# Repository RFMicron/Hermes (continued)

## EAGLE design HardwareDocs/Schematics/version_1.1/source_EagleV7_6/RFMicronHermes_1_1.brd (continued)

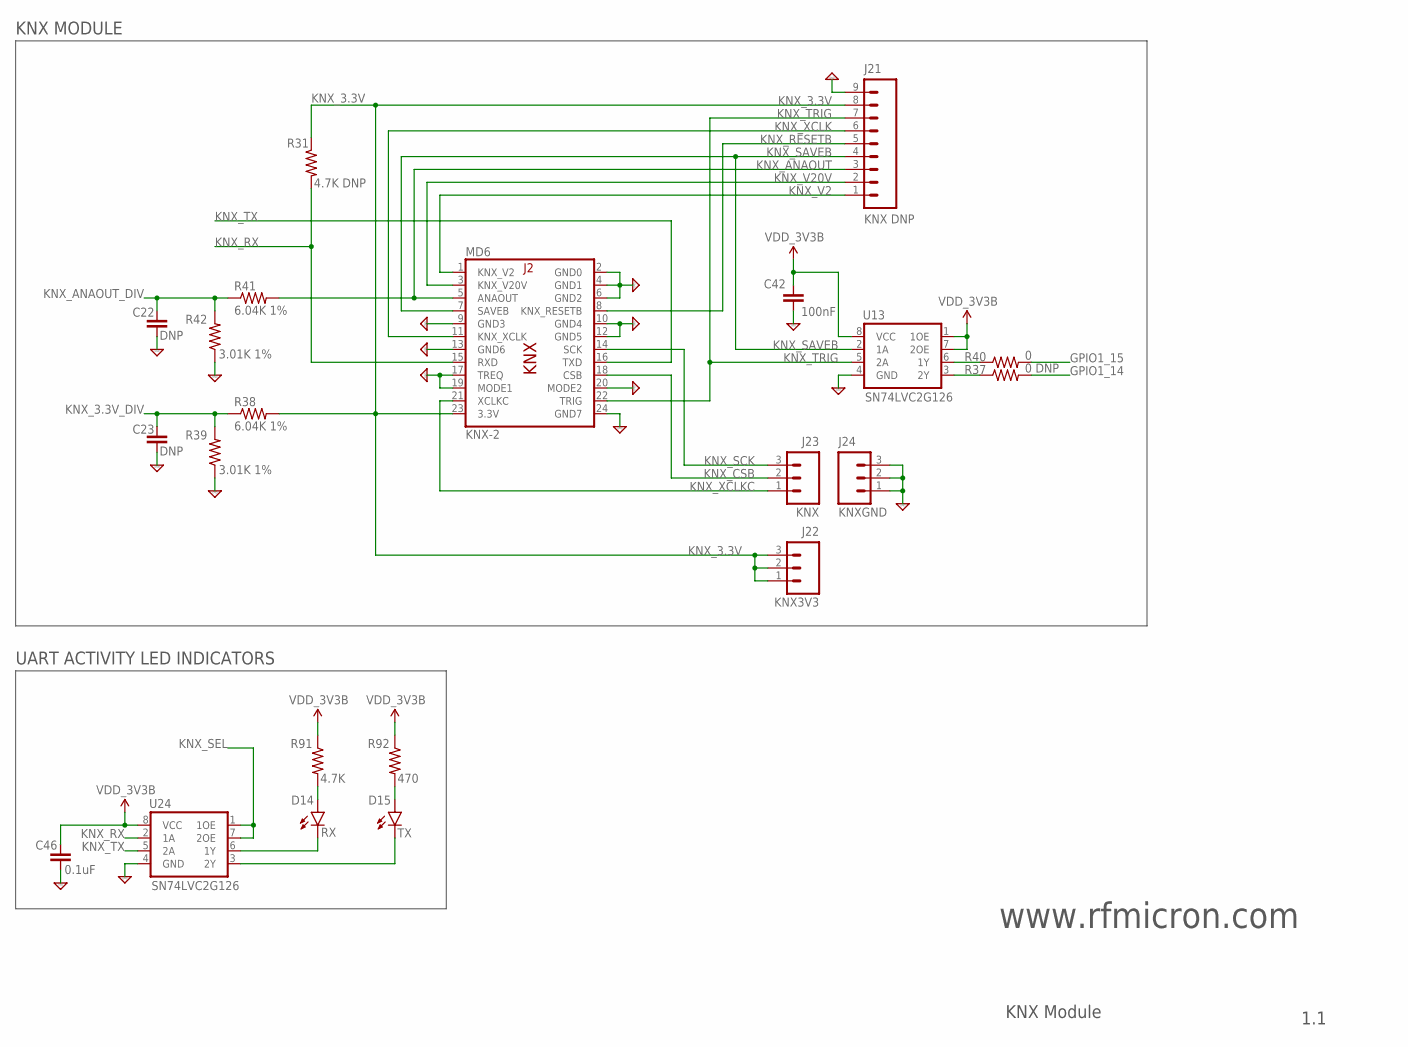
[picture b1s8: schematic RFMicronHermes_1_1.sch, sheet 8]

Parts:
C22, C23: DNP; C0603K
C42: 100nF; C0603K
C46: 0.1uF; C0603K
D14: RX; LED-1206
D15: TX; LED-1206
J21: KNX DNP; 1X09-SPECIAL
J22: KNX3V3; 1X03-SPECIAL
J23: KNX; 1X03-SPECIAL
J24: KNXGND; 1X03-SPECIAL
MD6: KNX-2; KNX-1
R31: 4.7K DNP; R0603
R37: 0 DNP; R0603
R38, R41: 6.04K 1%; R0603
R39, R42: 3.01K 1%; R0603
R40: 0; R0603
R91: 4.7K; R0603
R92: 470; R0603
U13, U24: SN74LVC2G126; SM8-TI-A

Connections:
GND: C22.2 (-), C23.2 (-), C42.2 (-), C46.1 (+), J21.9, J24.1, J24.2, J24.3, MD6.2 (GND0), MD6.4 (GND1), MD6.6 (GND2), MD6.9 (GND3), MD6.10 (GND4), MD6.12 (GND5), MD6.13 (GND6), MD6.17 (TREQ), MD6.19 (MODE1), MD6.20 (MODE2), MD6.24 (GND7), R39.1, R42.1, U13.4 (GND), U24.4 (GND); also elsewhere on the board
GPIO1_14: R37.2; also elsewhere on the board
GPIO1_15: R40.2; also elsewhere on the board
KNX_3.3V: J21.8, J22.1, J22.2, J22.3, MD6.23 (3.3V), R31.1, R38.2
KNX_3.3V_DIV: C23.1 (+), R38.1, R39.2; also elsewhere on the board
KNX_ANAOUT: J21.3, MD6.5 (ANAOUT), R41.2
KNX_ANAOUT_DIV: C22.1 (+), R41.1, R42.2; also elsewhere on the board
KNX_CSB: J23.2, MD6.18 (CSB)
KNX_RESETB: J21.5, MD6.8 (KNX_RESETB)
KNX_RX: MD6.15 (RXD), R31.2, U24.2 (1A); also elsewhere on the board
KNX_SAVEB: J21.4, MD6.7 (SAVEB), U13.2 (1A)
KNX_SCK: J23.3, MD6.14 (SCK)
KNX_SEL: U24.1 (1OE), U24.7 (2OE); also elsewhere on the board
KNX_TRIG: J21.7, MD6.22 (TRIG), U13.5 (2A)
KNX_TX: MD6.16 (TXD), U24.5 (2A); also elsewhere on the board
KNX_V2: J21.1, MD6.1 (KNX_V2)
KNX_V20V: J21.2, MD6.3 (KNX_V20V)
KNX_XCLK: J21.6, MD6.11 (KNX_XCLK)
KNX_XCLKC: J23.1, MD6.21 (XCLKC)
unnamed: R40.1, U13.6 (1Y)
unnamed: R37.1, U13.3 (2Y)
unnamed: D14.A, R91.2
unnamed: D15.A, R92.2
unnamed: D14.C, U24.6 (1Y)
unnamed: D15.C, U24.3 (2Y)
VDD_3V3B: C42.1 (+), C46.2 (-), R91.1, R92.1, U13.1 (1OE), U13.7 (2OE), U13.8 (VCC), U24.8 (VCC); also elsewhere on the board

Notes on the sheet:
www.rfmicron.com
1.1
KNX Module
UART ACTIVITY LED INDICATORS
KNX MODULE

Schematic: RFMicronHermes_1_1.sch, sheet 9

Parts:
C28: 10uF 16V; EIA3216
C29, C47: 0.1uF; C0603K
D4: DB2431200L; SC-110A-POWER_DIODE
D16: HB; LED-1206
D17: USER_LED; LED-1206
E2, E3, E4, E5, E6, E7: 1; MTHOLE4-40
F2: 3.5A; FUSE_OMNI-BLOCK-154
J11: +5V; POWER_JACK_PTH
J28: Test Connector; 2X7SM
J32: HEADER A; 2X13-SM
R76, R77, R78, R79, R80, R81: 10K; R0603
R93, R94: 4.7K; R0603
R98: 0; R0603
S1: Power; EVQ-PAC04M
S2: Reset; EVQ-PAC04M
S3: Up; EVQ-PAC04M
S4: Down; EVQ-PAC04M
S5: Right; EVQ-PAC04M
S6: Left; EVQ-PAC04M
S7: Enter; EVQ-PAC04M
U25: SN74LVC2G126; SM8-TI-A

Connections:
+5V: F2.1, J11.1 (PWR)
A0/CS: J28.1; also elsewhere on the board
A1/SI: J28.3; also elsewhere on the board
AIN4_SW: J32.7; also elsewhere on the board
AIN5_SW: J32.9; also elsewhere on the board
DOWN_BUT: R78.1, S4.1 (S), S4.2 (S1); also elsewhere on the board
EEPROM-WP: J28.13; also elsewhere on the board
ENTER_BUT: R81.1, S7.1 (S), S7.2 (S1); also elsewhere on the board
EXT_UART_RX: J28.11; also elsewhere on the board
EXT_UART_TX: J28.9; also elsewhere on the board
GND: C28.C (-), C29.2 (-), C47.1 (+), D4.A, E2.1, E3.1, E4.1, E5.1, E6.1, E7.1, J11.2 (GND), J11.3 (GNDBREAK), J28.14, J32.1, J32.13, J32.15, J32.25, R93.2, R94.2, S1.3, S1.4 (P1), S2.3, S2.4 (P1), S3.3, S3.4 (P1), S4.3, S4.4 (P1), S5.3, S5.4 (P1), S6.3, S6.4 (P1), S7.3, S7.4 (P1), U25.4 (GND); also elsewhere on the board
GPIO0_7: J32.21; also elsewhere on the board
GPIO0_20: J32.23; also elsewhere on the board
GPIO1_12: J32.14; also elsewhere on the board
GPIO1_13: J32.12; also elsewhere on the board
GPIO1_14: J32.19, R98.1; also elsewhere on the board
GPIO1_15: J32.17; also elsewhere on the board
GPIO2_3: J32.8; also elsewhere on the board
GPIO2_5: J32.10; also elsewhere on the board
I2C1_SCL: J32.16; also elsewhere on the board
I2C1_SDA: J32.18; also elsewhere on the board
LCD_TEST_V: J32.11; also elsewhere on the board
LED_HEARTBEAT: U25.2 (1A); also elsewhere on the board
LEFT_BUT: R80.1, S6.1 (S), S6.2 (S1); also elsewhere on the board
unnamed: D16.C, R93.1
unnamed: D17.C, R94.1
unnamed: R98.2, U25.5 (2A)
unnamed: D16.A, U25.6 (1Y)
unnamed: D17.A, U25.3 (2Y)
PWR_BUT: S1.1 (S), S1.2 (S1); also elsewhere on the board
RIGHT_BUT: R79.1, S5.1 (S), S5.2 (S1); also elsewhere on the board
SCL/SCLK: J28.7; also elsewhere on the board
SO: J28.5; also elsewhere on the board
SPI1_CS0: J28.2, J32.20; also elsewhere on the board
SPI1_D0: J28.6, J32.22; also elsewhere on the board
SPI1_D1: J28.4, J32.24; also elsewhere on the board
SPI1_SCLK: J28.8, J32.26; also elsewhere on the board
SYS_5V: J32.2; also elsewhere on the board
SYS_!RESET: R76.1, S2.1 (S), S2.2 (S1); also elsewhere on the board
UP_BUT: R77.1, S3.1 (S), S3.2 (S1); also elsewhere on the board
VDD_3V3B: C47.2 (-), J32.4, R76.2, R77.2, R78.2, R79.2, R80.2, R81.2, U25.1 (1OE), U25.7 (2OE), U25.8 (VCC); also elsewhere on the board
VDD_5V: C28.A (+), C29.1 (+), D4.C, F2.2, J32.6; also elsewhere on the board

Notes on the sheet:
www.rfmicron.com
1.1
Power Input, Connectors, Buttons, LEDs and Mounting Holes
POWER INPUT
EXTERNAL CONNECTORS
USER BUTTONS
LED INDICATION
MOUNTING HOLES

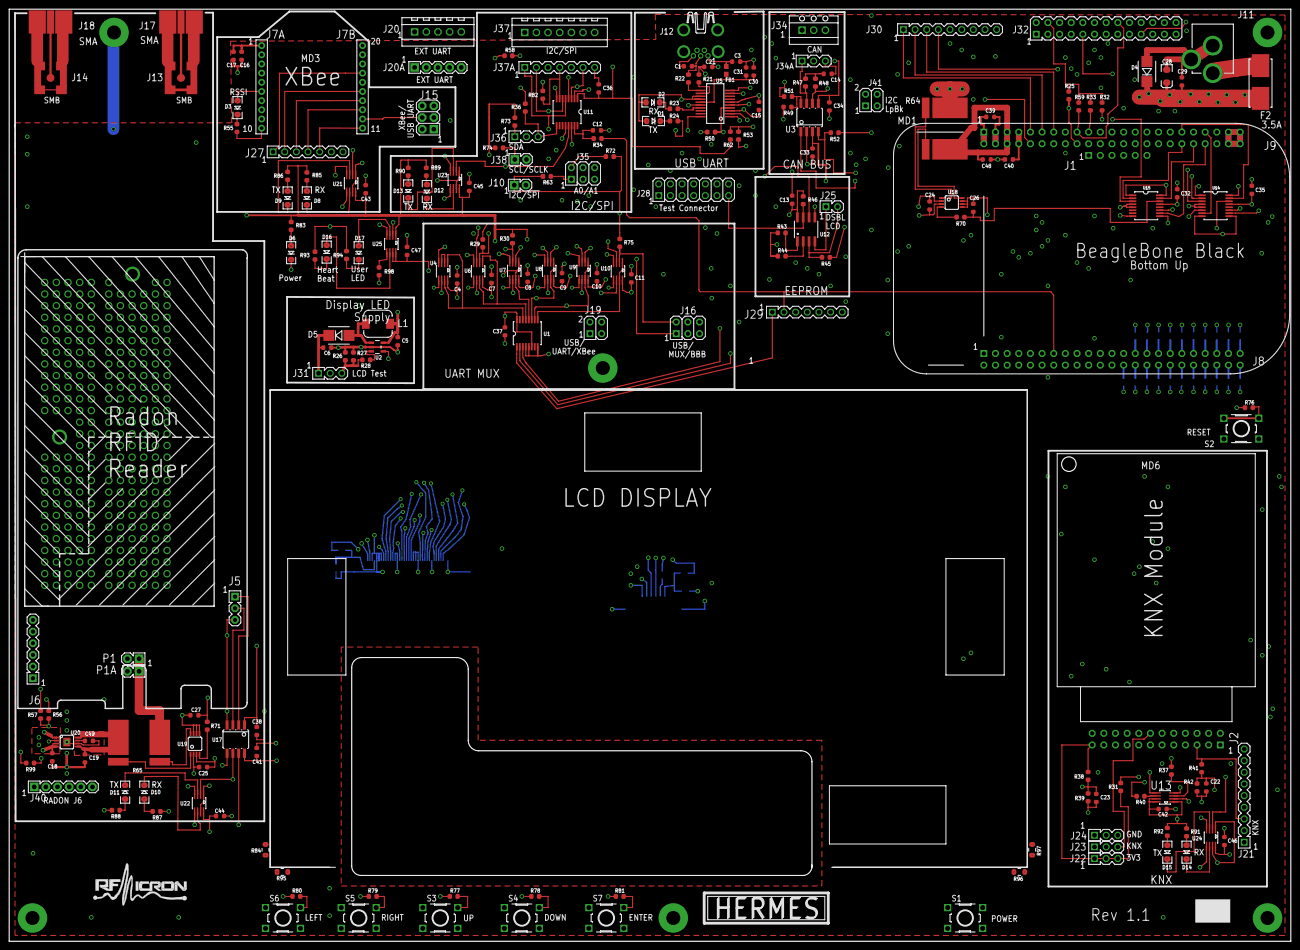
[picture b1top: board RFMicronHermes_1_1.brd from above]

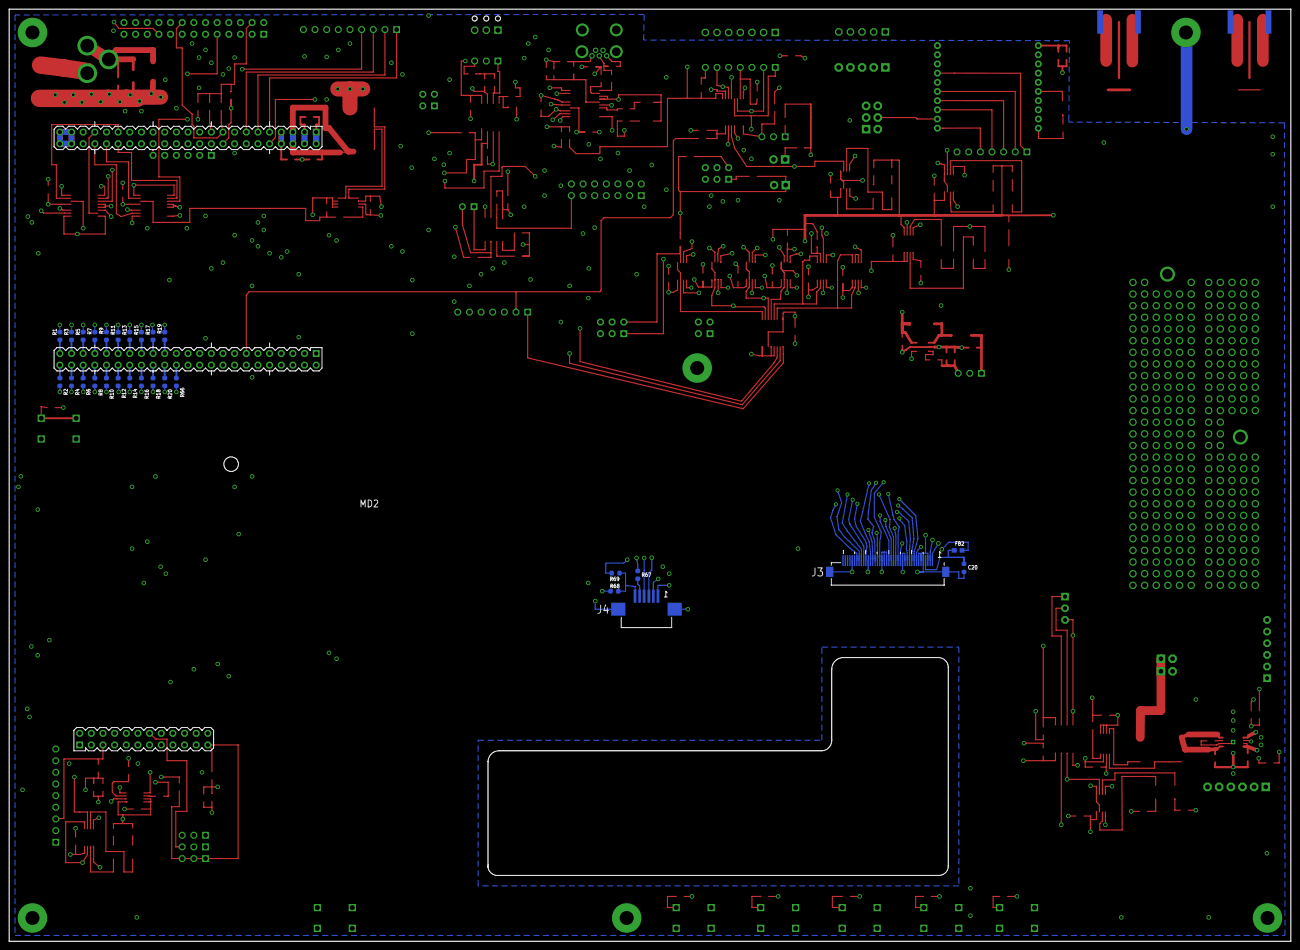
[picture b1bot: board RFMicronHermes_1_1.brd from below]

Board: 6 copper layers, 279.4 x 203.2 mm, 240 parts (26 on the bottom side), 230 nets.

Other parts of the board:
U$3: HERMES
U$62: RFMLOGO3B
U$80: SERNUM

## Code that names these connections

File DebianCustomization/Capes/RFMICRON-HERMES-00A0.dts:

/*
 * Copyright (C) 2016 RFMicron, Inc. - http://www.rfmicron.com/
 *
 * This program is free software; you can redistribute it and/or modify
 * it under the terms of the GNU General Public License version 2 as
 * published by the Free Software Foundation.
 */
/dts-v1/;
/plugin/;

/ {
	compatible = "ti,beaglebone-black";

	/* identification */
	part-number = "RFMICRON-HERMES";
	version = "00A0";

	/* state the resources this cape uses */
	exclusive-use =
		/* the pin header uses */
		"P8.45",	/* lcd: lcd_data0 */
		"P8.46",	/* lcd: lcd_data1 */
		"P8.43",	/* lcd: lcd_data2 */
		"P8.44",	/* lcd: lcd_data3 */
		"P8.41",	/* lcd: lcd_data4 */
		"P8.42",	/* lcd: lcd_data5 */
		"P8.39",	/* lcd: lcd_data6 */
		"P8.40",	/* lcd: lcd_data7 */
		"P8.37",	/* lcd: lcd_data8 */
		"P8.38",	/* lcd: lcd_data9 */
		"P8.36",	/* lcd: lcd_data10 */
		"P8.34",	/* lcd: lcd_data11 */
		"P8.35",	/* lcd: lcd_data12 */
		"P8.33",	/* lcd: lcd_data13 */
		"P8.31",	/* lcd: lcd_data14 */
		"P8.32",	/* lcd: lcd_data15 */
		"P8.27",	/* lcd: lcd_vsync */
		"P8.29",	/* lcd: lcd_hsync */
		"P8.28",	/* lcd: lcd_pclk */
		"P8.30",	/* lcd: lcd_ac_bias_en */
		"P8.26",	/* lcd: gpio1_29 */
		"P9.12",	/* led: gpio1_28 */
		"P9.14",	/* pwm: ehrpwm1a */
		"P9.15",	/* keys: gpio1_16 */
		"P9.23",	/* keys: gpio1_17 */
		"P9.16",	/* keys: gpio1_19 */
		"P9.27",	/* keys: gpio3_19 */
		"P8.18",	/* keys: gpio2_1 */
		/* the hardware IP uses */
		"gpio1_29",
		"gpio1_28",
		"gpio1_16",
		"gpio1_17",
		"gpio1_19",
		"gpio3_19",
		"gpio2_1",
		"lcd",
		"ehrpwm1a";

	fragment@0 {
		target = <&am33xx_pinmux>;
		__overlay__ {

			heartbeat_led: pinmux_heartbeat_led {
				pinctrl-single,pins = <
					0x078 0x2f	/* gpmc_ben1.gpio1_28, INPUT | PULLDIS | MODE7 */
				>;
			};

			pwm_bl_pins: pinmux_pwm_bl_pins {
				pinctrl-single,pins = <
					0x48 0x06       /* gpmc_a2.ehrpwm1a, OMAP_MUX_MODE6 | AM33XX_PIN_OUTPUT */
				>;
			};

			lcd_pins: pinmux_lcd_pins {
				pinctrl-single,pins = <
					0x7c 0x07	/* gpmc_csn0.gpio1_29, OUTPUT | MODE7 - LCD_DISP */
					0xa0 0x08	/* lcd_data0.lcd_data0, OMAP_MUX_MODE0 | AM33XX_PIN_OUTPUT | AM33XX_PULL_DISA */
					0xa4 0x08	/* lcd_data1.lcd_data1, OMAP_MUX_MODE0 | AM33XX_PIN_OUTPUT | AM33XX_PULL_DISA */
					0xa8 0x08	/* lcd_data2.lcd_data2, OMAP_MUX_MODE0 | AM33XX_PIN_OUTPUT | AM33XX_PULL_DISA */
					0xac 0x08	/* lcd_data3.lcd_data3, OMAP_MUX_MODE0 | AM33XX_PIN_OUTPUT | AM33XX_PULL_DISA */
					0xb0 0x08	/* lcd_data3.lcd_data3, OMAP_MUX_MODE0 | AM33XX_PIN_OUTPUT | AM33XX_PULL_DISA */
					0xb4 0x08	/* lcd_data5.lcd_data5, OMAP_MUX_MODE0 | AM33XX_PIN_OUTPUT | AM33XX_PULL_DISA */
					0xb8 0x08	/* lcd_data6.lcd_data6, OMAP_MUX_MODE0 | AM33XX_PIN_OUTPUT | AM33XX_PULL_DISA */
					0xbc 0x08	/* lcd_data7.lcd_data7, OMAP_MUX_MODE0 | AM33XX_PIN_OUTPUT | AM33XX_PULL_DISA */
					0xc0 0x08	/* lcd_data8.lcd_data8, OMAP_MUX_MODE0 | AM33XX_PIN_OUTPUT | AM33XX_PULL_DISA */
					0xc4 0x08	/* lcd_data9.lcd_data9, OMAP_MUX_MODE0 | AM33XX_PIN_OUTPUT | AM33XX_PULL_DISA */
					0xc8 0x08	/* lcd_data10.lcd_data10, OMAP_MUX_MODE0 | AM33XX_PIN_OUTPUT | AM33XX_PULL_DISA */
					0xcc 0x08	/* lcd_data11.lcd_data11, OMAP_MUX_MODE0 | AM33XX_PIN_OUTPUT | AM33XX_PULL_DISA */
					0xd0 0x08	/* lcd_data12.lcd_data12, OMAP_MUX_MODE0 | AM33XX_PIN_OUTPUT | AM33XX_PULL_DISA */
					0xd4 0x08	/* lcd_data13.lcd_data13, OMAP_MUX_MODE0 | AM33XX_PIN_OUTPUT | AM33XX_PULL_DISA */
					0xd8 0x08	/* lcd_data14.lcd_data14, OMAP_MUX_MODE0 | AM33XX_PIN_OUTPUT | AM33XX_PULL_DISA */
					0xdc 0x08	/* lcd_data15.lcd_data15, OMAP_MUX_MODE0 | AM33XX_PIN_OUTPUT | AM33XX_PULL_DISA */
					0xe0 0x00	/* lcd_vsync.lcd_vsync, OMAP_MUX_MODE0 | AM33XX_PIN_OUTPUT */
					0xe4 0x00	/* lcd_hsync.lcd_hsync, OMAP_MUX_MODE0 | AM33XX_PIN_OUTPUT */
					0xe8 0x00	/* lcd_pclk.lcd_pclk, OMAP_MUX_MODE0 | AM33XX_PIN_OUTPUT */
					0xec 0x00	/* lcd_ac_bias_en.lcd_ac_bias_en, OMAP_MUX_MODE0 | AM33XX_PIN_OUTPUT */
				>;
			};

			keys_pins: pinmux_keys_pins {
				pinctrl-single,pins = <
					0x040 0x2f	/* KEY_LEFT gpmc_a0.gpio1_16, INPUT | PULLDIS | MODE7 */
					0x044 0x2f	/* KEY_RIGHT gpmc_a1.gpio1_17, INPUT | PULLDIS | MODE7 */
					0x04c 0x2f 	/* KEY_UP gpmc_a3.gpio1_19, INPUT | PULLDIS | MODE7 */
					0x1A4 0x2f	/* KEY_DOWN mcasp0_fsr.gpio3_19, INPUT | PULLDIS | MODE7 */ 
					0x08c 0x2f	/* KEY_ENTER gpmc_clk_mux0.gpio2_1, INPUT | PULLDIS | MODE7 */
				>;
			};

		};
	};

	fragment@1 {
		target = <&epwmss1>;
		__overlay__ {
			status = "okay";
		};
	};

	fragment@2 {
		target = <&ehrpwm1>;
		__overlay__ {
			status = "okay";
		};
	};

	fragment@3 {
		target = <&ocp>;

		__overlay__ {

			/* avoid warning */
			#address-cells = <1>;
			#size-cells = <1>;

			backlight {
				compatible      = "pwm-backlight";
				pinctrl-names   = "default";
				pinctrl-0       = <&pwm_bl_pins>;
				status = "okay";

				pwms = <&ehrpwm1 0 500000 0>;
				pwm-names = "HERMES_LCD";
				brightness-levels = <0 1 2 3 4 5 6 7 8 9 10 11 12 13 14 15 16 17 18 19 20 21 22 23 24 25 26 27 28 29 30 31 32 33 34 35 36 37 38 39 40 41 42 43 44 45 46 47 48 49 50 51 52 53 54 55 56 57 58 59 60 61 62 63 64 65 66 67 68 69 70 71 72 73 74 75 76 77 78 79 80 81 82 83 84 85 86 87 88 89 90 91 92 93 94 95 96 97 98 99 100>;
				default-brightness-level = <100>; 
			};

			gpio-leds {
				compatible = "gpio-leds";
				pinctrl-names = "default";

				pinctrl-0 = <&heartbeat_led>;

				hermes-led0 {
					label = "hermes:green:usr0";
					gpios = <&gpio2 28 0>;
					linux,default-trigger = "heartbeat";
					default-state = "off";
				};

			};

			gpio_keys {
				compatible = "gpio-keys";
				pinctrl-names = "default";
				pinctrl-0 = <&keys_pins>;

				#address-cells = <1>;
				#size-cells = <0>;

				button@1 {
					debounce_interval = <50>;
					linux,code = <105>;
					label = "left";
					gpios = <&gpio2 16 0x1>;
					gpio-key,wakeup;
					autorepeat;
				};
				button@2 {
					debounce_interval = <50>;
					linux,code = <106>;
					label = "right";
					gpios = <&gpio2 17 0x1>;
					gpio-key,wakeup;
					autorepeat;
				};
				button@3 {
					debounce_interval = <50>;
					linux,code = <103>;
					label = "up";
					gpios = <&gpio2 19 0x1>;
					gpio-key,wakeup;
					autorepeat;
				};
				button@4 {
					debounce_interval = <50>;
					linux,code = <108>;
					label = "down";
					gpios = <&gpio4 19 0x1>;
					gpio-key,wakeup;
					autorepeat;
				};
				button@5 {
					debounce_interval = <50>;
					linux,code = <28>;
					label = "enter";
					gpios = <&gpio3 1 0x1>;
					gpio-key,wakeup;
				};
			};

			/* Settings for Newhaven NHD-7.0-800480EF-ATXV#-CTP */
			panel {
				compatible = "tilcdc,panel";
				pinctrl-names = "default";
				pinctrl-0 = <&lcd_pins>;
				panel-info {
					ac-bias           = <255>;
					ac-bias-intrpt    = <0>;
					dma-burst-sz      = <16>;
					bpp               = <16>;
					fdd               = <0x80>;
					tft-alt-mode      = <0>;
					stn-565-mode      = <0>;
					mono-8bit-mode    = <0>;
					sync-edge         = <0>;
					sync-ctrl         = <1>;
					raster-order      = <0>;
					fifo-th           = <0>;
				};
				display-timings {
					native-mode = <&timing0>;
					timing0: 800x480 {
						hactive         = <800>;
						vactive         = <480>;
						hback-porch     = <88>;
						hfront-porch    = <40>;
						hsync-len       = <48>;
						vback-porch     = <32>;
						vfront-porch    = <13>;
						vsync-len       = <3>;
						clock-frequency = <30000000>;
						hsync-active    = <0>;
						vsync-active    = <0>;
					};
				};
			};

			fb {
				compatible = "ti,am33xx-tilcdc";
				reg = <0x4830e000 0x1000>;
				interrupt-parent = <&intc>;
				interrupts = <36>;
				ti,hwmods = "lcdc";
				ti,power-gpio = <&gpio2 29 0x0>;
				ti,allow-non-reduced-blanking-modes;
			};

		};
	};
};

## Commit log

2016-02-20 Initial commit with demo app source code
2016-02-21 Added hardware and software documentation
2016-02-22 Added schematics, RUI Guide, and Developer's Guide
2016-03-01 Added documentation for subsystem hardware components
2016-03-11 Updated schematics version and added Eagle V7.5 source files
2016-03-11 Added manufacturing test source code
2016-03-11 Added BeagleBone Debian customization files
2016-03-21 Added file with links to BeagleBone Black images
2016-03-21 Corrected files with links to BeagleBone Black images
2016-03-21 Added README file to DebianCustomization folder
2016-03-21 Updated README.md file
2016-03-21 Updated web links in a couple of files
2016-03-21 Added file with links to Qt cross-compiler components
2016-03-25 Corrected cape files needed to enable HDMI
2016-03-25 Added new documents
2016-04-27 Version 1.1.0 of demo app
2016-04-29 Added AS3993 firmware
2016-07-15 Added version 1.1 of board schematics, gerbers and BoM
    Reorganized schematics folder in order to add new version 1.1 and
    coexist with previous version 1.0
2016-07-22 Updated README.md
    Fixed web links and added file for release 1.1
2016-07-22 Update Qt-Cross-Compiler-Components.md
    Fixed link to Qt-CrossCompiler-Components
2016-07-22 Update BeagleBone_Black_Images.md
    Fixed links and added link to new released version 1.1
2016-10-06 Documentation update regarding J16
    Updated two documents with the recommended default position for the
    jumpers on J16 and added warning note about having the jumpers in place
    without having an external computer connected to the Hermes kit USB
    connector (J12)
2018-04-07 Create bleuberry
2018-04-09 Create blueberry
2018-10-20 Create bbb
